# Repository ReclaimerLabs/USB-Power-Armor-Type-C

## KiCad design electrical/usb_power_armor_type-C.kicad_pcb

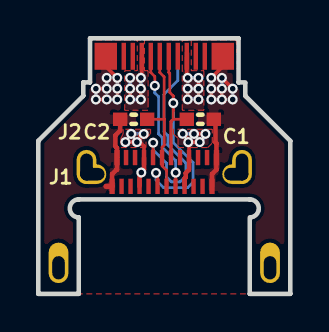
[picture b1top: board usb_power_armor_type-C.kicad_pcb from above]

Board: 2 copper layers, 14.0 x 14.2 mm, 4 parts (0 on the bottom side), 6 nets.

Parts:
C1, C2: 0.1 uF; 0603_np
J1: USB-C_Female; USB-C_Female_Mid_Mount_Dual_SMT_RA
J2: USB-C_Plug; USB-C_Plug_Mid_Mount

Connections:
/CC1: J1.A5, J2.B5
/CC2: J1.B5, J2.A5
/DN: C1.1, J1.A7, J1.B7, J2.A7
/DP: C2.1, J1.A6, J1.B6, J2.A6
/Vbus: J1.A4, J1.A9, J1.B4, J1.B9, J2.A4, J2.A9, J2.B4, J2.B9
GND: C1.2, C2.2, J1.A1, J1.A12, J1.B1, J1.B12, J2.A1, J2.A12, J2.B1, J2.B12

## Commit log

2016-02-18 :space_invader: Added .gitattributes
